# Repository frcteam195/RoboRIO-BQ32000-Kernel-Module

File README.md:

# RoboRIO BQ32000 Kernel Module

Run the RoboRIOSetup.sh script on the RoboRIO to build and install the module and startup script. Step by step instructions instead of the script are below

_______________________________________________________

Adding an RTC to the RoboRIO with the BQ32000 from TI

RTC Datasheet:  
http://www.ti.com/lit/ds/symlink/bq32000.pdf

Started off with the BQ32000 Module from Evola:  
https://evola.fr/en/breakout-boards/813-real-time-clock-module-bq32000.html

It is wired up to the i2c port on the RoboRIO like this:  
```
RTC     rRIO  
SDA-----SDA  
SCL-----SCL  
VCC-----3V3  
GND-----GND  
```

Next, pulled the kernel driver from the NI git repo here:  
https://raw.githubusercontent.com/ni/linux/nilrt_pub/16.0/4.1/drivers/rtc/rtc-bq32k.c

This is a stock driver for Linux mainline from what I can tell.

The stock driver file was modified to remove the need to do anything special to enable the trickle charge feature.  This is a hack but it works for this module on this platform.

This is built on the RoboRIO using these directions from NI:  
https://forums.ni.com/t5/NI-Linux-Real-Time-Documents/Tutorial-Adding-Kernel-Modules-on-NI-Linux-Real-Time/ta-p/3527186

Note, you may need to add coreutils using opkg.  
You will also need to add i2c-tools using opkg.

Summary of steps from the NI Document: 
- Pull down these files into a local directory.
- run ```source /usr/local/natinst/tools/versioning_utils.sh```
- run ```setup_versioning_env```
- run ```versioning_call make```
- run ```cp rtc-bq32k.ko /lib/modules/`uname -r`/kernel```
- run ```depmod```

You should be able to run ```i2cdetect -y 2``` and it will show something like this:  
```
admin@roboRIO-900-FRC:~/rtc-bq32k# i2cdetect -y 2  
     0  1  2  3  4  5  6  7  8  9  a  b  c  d  e  f  
00:          -- -- -- -- -- -- -- -- -- -- -- -- --  
10: -- -- -- -- -- -- -- -- -- -- -- -- -- -- -- --  
20: -- -- -- -- -- -- -- -- -- -- -- -- -- -- -- --  
30: -- -- -- -- -- -- -- -- -- -- -- -- -- -- -- --  
40: -- -- -- -- -- -- -- -- -- -- -- -- -- -- -- --  
50: -- -- -- -- -- -- -- -- -- -- -- -- -- -- -- --  
60: -- -- -- -- -- -- -- -- 68 -- -- -- -- -- -- --  
70: -- -- -- -- -- -- -- --                          
```

The 68 indicates that the device has been found.

You can now run this to instantiate the device:  
```echo bq32000 0x68 | tee /sys/class/i2c-adapter/i2c-2/new_device```

If you run ```i2cdetect -y 2``` again it will show "UU" instead of 68 indicating that the device is active:
```
admin@roboRIO-900-FRC:~/rtc-bq32k# i2cdetect -y 2  
     0  1  2  3  4  5  6  7  8  9  a  b  c  d  e  f  
00:          -- -- -- -- -- -- -- -- -- -- -- -- --  
10: -- -- -- -- -- -- -- -- -- -- -- -- -- -- -- --  
20: -- -- -- -- -- -- -- -- -- -- -- -- -- -- -- --  
30: -- -- -- -- -- -- -- -- -- -- -- -- -- -- -- --  
40: -- -- -- -- -- -- -- -- -- -- -- -- -- -- -- --  
50: -- -- -- -- -- -- -- -- -- -- -- -- -- -- -- --  
60: -- -- -- -- -- -- -- -- UU -- -- -- -- -- -- --  
70: -- -- -- -- -- -- -- --                          
```

Running ```dmesg``` will show something like this:  
```
[   53.975048] bq32k 2-0068: Enabling trickle charge!  
[   53.975951] bq32k 2-0068: Enabled trickle RTC battery charge.  
[   53.976784] bq32k 2-0068: rtc core: registered bq32k as rtc0  
```

You can then proceed to set the clock and read from it:  
Setting the clock: ```hwclock.util-linux --systohc --utc -f /dev/rtc0```  
Reading from it: ```hwclock.util-linux -r -f /dev/rtc0```

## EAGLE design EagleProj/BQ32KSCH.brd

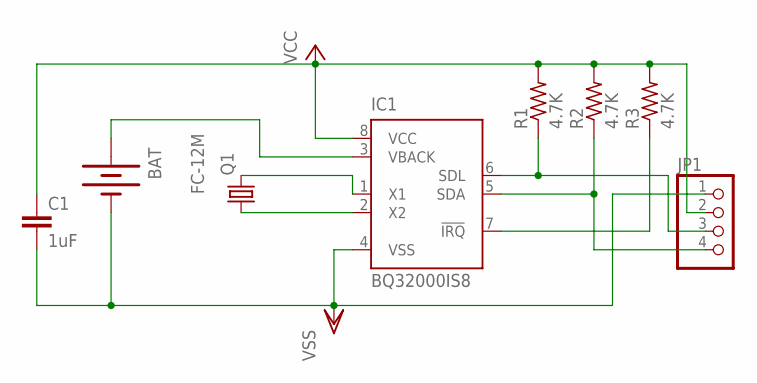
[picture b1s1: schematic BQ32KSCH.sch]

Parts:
BAT: CR1025-HOLDER
C1: 1uF; C3216
IC1: BQ32000IS8; SO-08
JP1: PINHD-1X4; 1X04
Q1: FC-12M
R1, R2, R3: 4.7K; R0402

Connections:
unnamed: IC1.1 (X1), Q1.2
unnamed: IC1.2 (X2), Q1.1
unnamed: IC1.6 (SDL), JP1.3, R1.1
unnamed: IC1.5 (SDA), JP1.4, R2.1
unnamed: IC1.7 (!IRQ), R3.1
unnamed: BAT.PRWP1 (PWRP), BAT.PWRP2 (PWRP), IC1.3 (VBACK)
VCC: C1.1, IC1.8 (VCC), JP1.2, R1.2, R2.2, R3.2
VSS: BAT.PWRM1 (PWRM), BAT.PWRM2 (PWRM), C1.2, IC1.4 (VSS), JP1.1

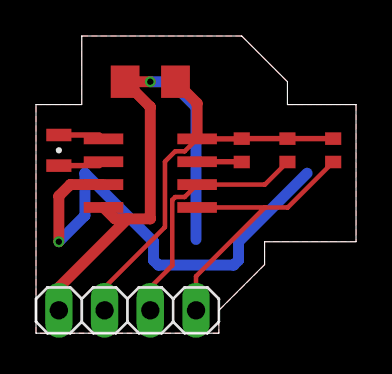
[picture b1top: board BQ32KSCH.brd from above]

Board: 2 copper layers, 17.8 x 16.5 mm, 8 parts (1 on the bottom side), 8 nets.

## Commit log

2019-01-17 Remove precompiled binary
2019-01-17 Modify C file
2019-01-17 Convert spaces to tabs
2019-01-18 Add eagle project for circuit board and BOM
2019-01-18 Update to setup script
